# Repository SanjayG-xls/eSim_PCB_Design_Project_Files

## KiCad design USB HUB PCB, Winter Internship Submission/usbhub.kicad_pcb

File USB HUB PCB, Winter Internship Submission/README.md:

# QUADLINK — QL-04

**USB 2.0 High-Speed Hub | FOSSEE eSim Internship — Task 7**

QL-04 is a custom USB hub PCB based on the Microchip USB2514B. It connects a single USB-A host interface to three USB-A downstream ports and one USB-C downstream port, with individual port power control and ESD protection.

## Specifications

| Parameter | Specification |
| :--- | :--- |
| Hub controller | USB2514B |
| Upstream | 1 × USB-A male |
| Downstream | 3 × USB-A female + 1 × USB-C |
| USB standard | USB 2.0 High-Speed |
| Signaling rate | Up to 480 Mbps, shared across ports |
| Input power | 5 V USB bus power |
| Local supply | 3.3 V |
| Clock | 24 MHz |

## Circuit design

- **USB2514B:** Four-port USB hub controller.
- **AP2112K-3.3:** Local voltage regulation and supply filtering.
- **TPS2553:** Individual port power switching and overcurrent fault signaling.
- **STUSB1602:** USB-C configuration and attachment detection.
- **74LVC1G04 / 74LVC1G08:** USB-C VBUS enable logic.
- **USBLC6-2SC6:** ESD protection for USB data lines.
- **Shield and debug:** Parallel RC shield bonding and accessible test points.

## PCB layout

The layout uses five USB differential pairs, short clock connections, local decoupling, wider power tracks and clearly labeled interfaces. The USB data pairs target 90 Ω differential impedance, with a nominal trace width of 0.266 mm and gap of 0.200 mm.

### Copper stackup

The PCB uses four copper layers, with routing primarily on the outer layers and internal copper pours for ground and power distribution. The nominal impedance settings require manufacturer-specific verification.

## Design verification

The recorded ERC and DRC results show zero reported errors and warnings under the enabled checks, and DRC reports zero unconnected items.

The recorded verification results also show ignored checks and ERC exclusions; schematic parity was not run in the displayed DRC result. These results are design-stage checks, not hardware validation.

## Project files

| File / folder | Description |
| :--- | :--- |
| `usbhub.kicad_sch` | Editable schematic |
| `usbhub.kicad_pcb` | PCB layout |
| `usbhub.kicad_pro` | KiCad project settings |
| `usbhub.kicad_dru` | Custom design rules |
| `usbhub.kicad_prl` | Local project preferences |
| `usbhub.proj` | eSim project configuration |
| `fp-lib-table`, `sym-lib-table` | Library mappings |
| `STUSB1602AQTR/`, `TPS2553DBVT/`, `USB_Hub_Custom.pretty/` | Imported and custom libraries |
| `images/` | README banner |

## Opening the project

1. Clone or download the complete project folder.
2. Open the project using eSim and its KiCad-based design tools.
3. Check the included footprint, symbol and 3D model paths.
4. Open the schematic and PCB, run ERC/DRC and inspect the 3D view.

The design was edited using KiCad 9-based tools. Full compatibility with the required eSim 2.3/2.5 environment should be verified before submission.

## Project status

Schematic capture, footprint assignment, PCB routing and design-stage verification are complete. Fabrication and physical testing have not been performed. USB power budgeting, source configuration and signal integrity require further validation before hardware deployment.

---

**Designed by Sanjay G.**  
Department of VLSI Design and Technology, Chennai Institute of Technology  
FOSSEE eSim winter Internship — 2026 | Task 7

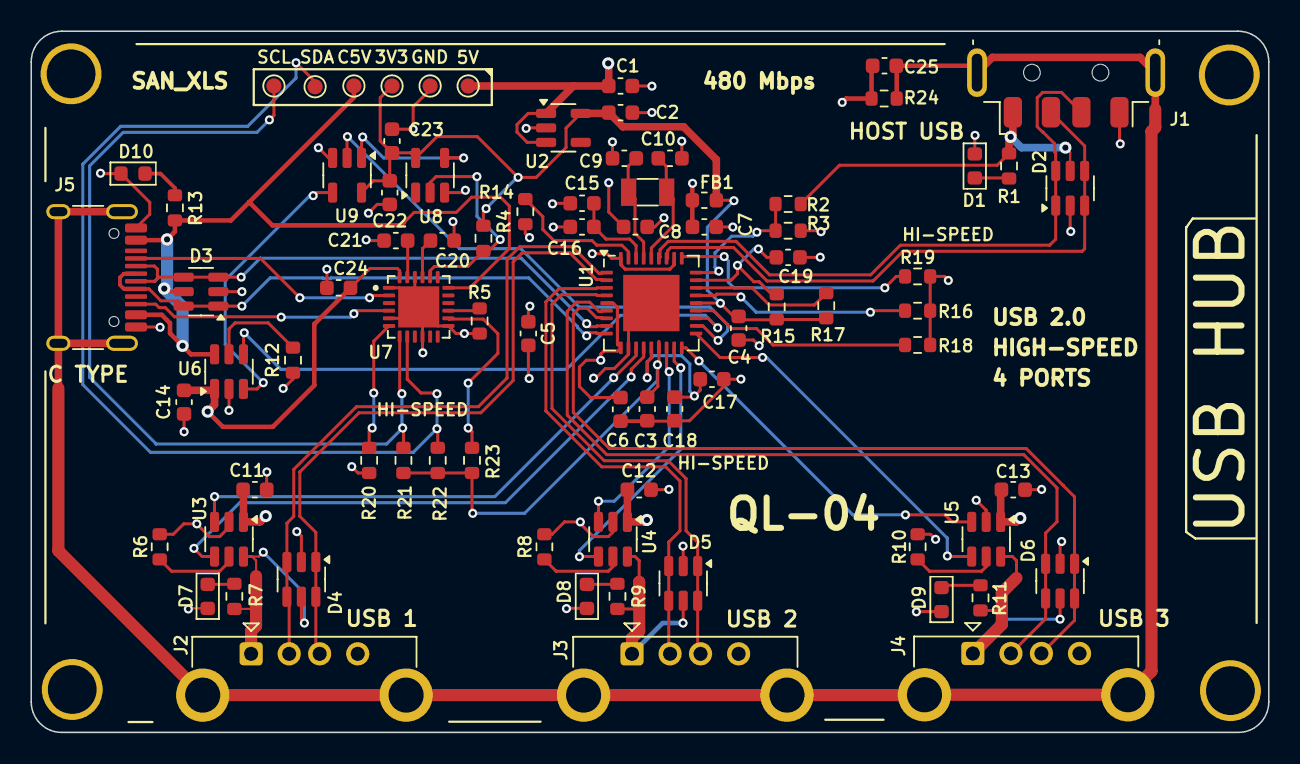
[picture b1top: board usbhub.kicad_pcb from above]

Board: 4 copper layers, 81.2 x 46.0 mm, 81 parts (0 on the bottom side), 59 nets.

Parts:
3V3, 5V: TestPoint; TestPoint_Pad_D1.0mm
C1, C2: 1uF; C_0603_1608Metric
C3, C4, C5, C6, C7, C8, C11, C12, C13, C14, C16, C18, C25: 100 nF; C_0603_1608Metric
C5V: TestPoint; TestPoint_Pad_D1.0mm
C9, C10: 18 pF; C_0603_1608Metric
C15, C17: 10 nF; C_0603_1608Metric
C19, C20, C21, C24: 1 µF; C_0603_1608Metric
C22, C23: 100nF; C_0603_1608Metric
D1, D7, D8, D9, D10: Green LED; LED_0603_1608Metric
D2, D3, D4, D5, D6: USBLC6-2SC6; SOT-23-6
FB1: 600R@100MHz; L_0603_1608Metric
GND: TestPoint; TestPoint_Pad_D1.0mm
J1: USB_A; USB_A_Molex_48037-2200_Horizontal
J2, J3, J4: USB_A_Female; USB_A_Kycon_KUSBX-AS1N-B_Horizontal
J5: USB_C_Receptacle_USB2.0_16P; USB_C_Receptacle_HRO_TYPE-C-31-M-12
R1, R7, R9, R11, R13: 2.2 kΩ; R_0603_1608Metric
R2, R3, R16, R18, R19: 100 kΩ; R_0603_1608Metric
R4, R15, R17: 10 kΩ; R_0603_1608Metric
R5, R20, R23: 10k; R_0603_1608Metric
R6, R8, R10, R12: 226kΩ; R_0603_1608Metric
R14: 12 kΩ; R_0603_1608Metric
R21, R22: 4.7kΩ; R_0603_1608Metric
R24: 330 Ω; R_0603_1608Metric
SCL: TestPoint; TestPoint_Pad_D1.0mm
SDA: TestPoint; TestPoint_Pad_D1.0mm
U1: USB2514B_Bi; QFN-36-1EP_6x6mm_P0.5mm_EP3.7x3.7mm
U2: AP2112K-3.3; SOT-23-5
U3, U4, U5, U6: TPS2553DBVT; SOT-23-6
U7: STUSB1602AQTR; QFN50P400X400X100-25N
U8: 74LVC1G04; SOT-23-5
U9: 74LVC1G08; SOT-23-5
Y1: 24 MHz; Crystal_SMD_3215-2Pin_3.2x1.5mm

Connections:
/+3V3: 3V3.1, C2.1, C3.2, C4.2, C22.1, C23.1, FB1.1, R4.1, R15.1, R17.1, R21.2, R22.2, R23.1, U1.15 (VDD33), U1.23 (VDD33), U2.5 (VOUT), U8.5 (VCC), U9.5 (VCC)
/+3V3_A: C5.2, C6.2, C7.2, C8.2, FB1.2, U1.5 (VDDA33), U1.10 (VDDA33), U1.29 (VDDA33), U1.36 (VDDA33)
/RESET_N: C19.2, R15.2, U1.26 (RESET_N)
/SCL: R21.1, SCL.1, U7.7 (SCL)
/SDA: R22.1, SDA.1, U7.8 (SDA)
/USB_5V_IN: 5V.1, C1.1, C11.1, C12.1, C13.1, C14.1, C24.1, D2.5 (VBUS), J1.1 (VBUS), R1.2, R2.1, U2.1 (VIN), U2.3 (EN), U3.1 (IN), U4.1 (IN), U5.1 (IN), U6.1 (IN), U7.24 (VDD)
/USB_A1_5V: D4.5 (VBUS), J2.1 (VBUS), R7.1, U3.6 (OUT)
/USB_A1_EN: U1.12 (PRTPWR1/BC_EN1), U3.3 (EN)
/USB_A1_FAULT: U1.13 (OCS_N1), U3.4 (~FAULT)
/USB_A2_5V: D5.5 (VBUS), J3.1 (VBUS), R9.1, U4.6 (OUT)
/USB_A2_EN: U1.16 (PRTPWR2/BC_EN2), U4.3 (EN)
/USB_A2_FAULT: U1.17 (OCS_N2), U4.4 (~FAULT)
/USB_A3_5V: D6.5 (VBUS), J4.1 (VBUS), R11.1, U5.6 (OUT)
/USB_A3_EN: U1.18 (PRTPWR3/BC_EN3), U5.3 (EN)
/USB_A3_FAULT: U1.19 (OCS_N3), U5.4 (~FAULT)
/USB_C_5V: C5V.1, D3.5 (VBUS), J5.A4 (VBUS), J5.A9 (VBUS), J5.B4 (VBUS), J5.B9 (VBUS), R13.1, U6.6 (OUT), U7.18 (VBUS_SENSE)
/USB_C_ATTACHED_EN: U8.4, U9.1
/USB_C_CC1: J5.A5 (CC1), U7.2 (CC1)
/USB_C_CC2: J5.B5 (CC2), U7.4 (CC2)
/USB_C_FAULT: U1.21 (OCS_N4), U6.4 (~FAULT)
/USB_C_FINAL_EN: U6.3 (EN), U9.4
/USB_C_HUB_PWR_EN: U1.20 (PRTPWR4/BC_EN4), U9.2
/USB_C_SRC_EN_N: R4.2, U7.20 (VBUS_EN_SRC), U8.2
/USB_DN1_N: D4.3 (I/O2), D4.4 (I/O2), J2.2 (D-), U1.1 (USBDM_DN1/PRT_DIS_M1)
/USB_DN1_P: D4.1 (I/O1), D4.6 (I/O1), J2.3 (D+), U1.2 (USBDP_DN1/PRT_DIS_P1)
/USB_DN2_N: D5.3 (I/O2), D5.4 (I/O2), J3.2 (D-), U1.3 (USBDM_DN2/PRT_DIS_M2)
/USB_DN2_P: D5.1 (I/O1), D5.6 (I/O1), J3.3 (D+), U1.4 (USBDP_DN2/PRT_DIS_P2)
/USB_DN3_N: D6.3 (I/O2), D6.4 (I/O2), J4.2 (D-), U1.6 (USBDM_DN3/PRT_DIS_M3)
/USB_DN3_P: D6.1 (I/O1), D6.6 (I/O1), J4.3 (D+), U1.7 (USBDP_DN3/PRT_DIS_P3)
/USB_DN4_N: D3.3 (I/O2), D3.4 (I/O2), J5.A7 (D-), J5.B7 (D-), U1.8 (USBDM_DN4/PRT_DIS_M4)
/USB_DN4_P: D3.1 (I/O1), D3.6 (I/O1), J5.A6 (D+), J5.B6 (D+), U1.9 (USBDP_DN4/PRT_DIS_P4)
/USB_SHIELD: C25.1, J1.5 (Shield), J2.5 (Shield), J3.5 (Shield), J4.5 (Shield), J5.S1 (SHIELD), R24.1
/USB_UP_N: D2.3 (I/O2), D2.4 (I/O2), J1.2 (D-), U1.30 (USBDM_UP)
/USB_UP_P: D2.1 (I/O1), D2.6 (I/O1), J1.3 (D+), U1.31 (USBDP_UP)
GND: C1.2, C2.2, C3.1, C4.1, C5.1, C6.1, C7.1, C8.1, C9.2, C10.1, C11.2, C12.2, C13.2, C14.2, C15.2, C16.2, C17.2, C18.2, C19.1, C20.2, C21.1, C22.2, C23.2, C24.2, C25.2, D1.1 (K), D2.2 (GND), D3.2 (GND), D4.2 (GND), D5.2 (GND), D6.2 (GND), D7.1 (K), D8.1 (K), D9.1 (K), D10.1 (K), GND.1, J1.4 (GND), J2.4 (GND), J3.4 (GND), J4.4 (GND), J5.A1 (GND), J5.A12 (GND), J5.B1 (GND), J5.B12 (GND), R3.2, R5.1, R6.1, R8.1, R10.1, R12.1, R14.1, R16.1, R18.1, R19.1, R20.1, R24.2, U1.11 (TEST), U1.37 (VSS), U2.2 (GND), U3.2 (GND), U4.2 (GND), U5.2 (GND), U6.2 (GND), U7.1 (CC1DB), U7.5 (CC2DB), U7.10 (GND), U7.13 (ADDR0), U7.22 (VSYS), U7.25 (EP(GND)), U8.3 (GND), U9.3 (GND)
unnamed: D1.2 (A), R1.1
unnamed: D7.2 (A), R7.2
unnamed: D8.2 (A), R9.2
unnamed: D9.2 (A), R11.2
unnamed: D10.2 (A), R13.2
unnamed: C17.1, C18.1, U1.14 (CRFILT)
unnamed: R17.2, U1.25 (HS_IND/CFG_SEL1)
unnamed: C15.1, C16.1, U1.34 (PLLFILT)
unnamed: R14.2, U1.35 (RBIAS)
unnamed: R16.2, U1.24 (SCL/SMBCLK/CFG_SEL0)
unnamed: R18.2, U1.22 (SDA/SMBDATA/NON_REM1)
unnamed: R19.2, U1.28 (SUSP_IND/LOCAL_PWR/NON_REM0)
unnamed: R2.2, R3.1, U1.27 (VBUS_DET)
unnamed: C9.1, U1.33 (XTALIN/CLKIN), Y1.2
unnamed: C10.2, U1.32 (XTALOUT), Y1.1
unnamed: R6.2, U3.5 (ILIM)
unnamed: R8.2, U4.5 (ILIM)
unnamed: R10.2, U5.5 (ILIM)
unnamed: R12.2, U6.5 (ILIM)
unnamed: R23.2, U7.14 (MISO)
unnamed: R20.2, U7.6 (RESET)
unnamed: R5.2, U7.15 (TX_EN)
unnamed: C20.1, U7.21 (VREG_1V2)
unnamed: C21.2, U7.23 (VREG_2V7)
